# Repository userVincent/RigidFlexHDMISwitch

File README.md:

# Rigid Flex HDMI Switch PCB - Eagle Design

## Introduction
This document provides an overview of a Rigid Flex HDMI Switch PCB designed using Eagle..

## Design rules
- According to the design guide from Wurth Electronics, extra mechanical layers are utilized to 
denote the flexible and rigid sections of the PCB. The flexible portion of the PCB is outlined 
on Layer 113 (flex), while Layer 114 (rigid) is used to delineate the rigid section.
- The differential pairs in the design are routed with a spacing of 150 micrometers (um) and a 
trace width of 260um. This configuration ensures that the differential pairs maintain their 
characteristic impedance, which is crucial for signal integrity. Additionally, careful attention 
has been paid to maximize the distance between different differential pairs. This strategy is 
employed to minimize crosstalk.
- In this PCB design, Flex1 is the ground layer, providing a return path for current. Flex2 is the 
VCC layer, distributing power to the components. The top layer primarily carries signal traces, 
while the bottom layer is used for both signal routing and distributing a +5V power supply.
-  According to the design guide from Wurth Electronics, two additional (unconnected) tracks 
are incorporated on the outer edges of the PCB. This design feature is intended to enhance 
the rigidity of the flex section and decrease the likelihood of tearing, thereby improving the 
durability and longevity of the PCB.
- To ensure efficient power distribution and adequate heat dissipation for power components 
on the top layer, the design includes multiple vias and planes (top layer). These features 
enhance connectivity and allow heat to spread out efficiently.
- The decoupling capacitors for the TDMS351 are strategically positioned on the bottom layer, 
directly beneath the IC. This placement is chosen to ensure effective decoupling, providing a 
short path for current transients and reducing noise. This arrangement is also due to space 
constraints on the top layer, making the bottom layer a practical choice for accommodating 
these components.

## Layer Configuration
- **Top Layer:** Primarily for signal traces.
- **Flex1:** Ground layer for current return path.
- **Flex2:** VCC layer for power distribution.
- **Bottom Layer:** Used for signal routing and a +5V power supply.

## PCB Preview
- **Routing View**
  
- **Top View**  
  
- **Bottom View**  

## Conclusion
This README provides a basic guide to a Rigid Flex HDMI Switch PCB. For detailed design files and further information, refer to the included Eagle project files.

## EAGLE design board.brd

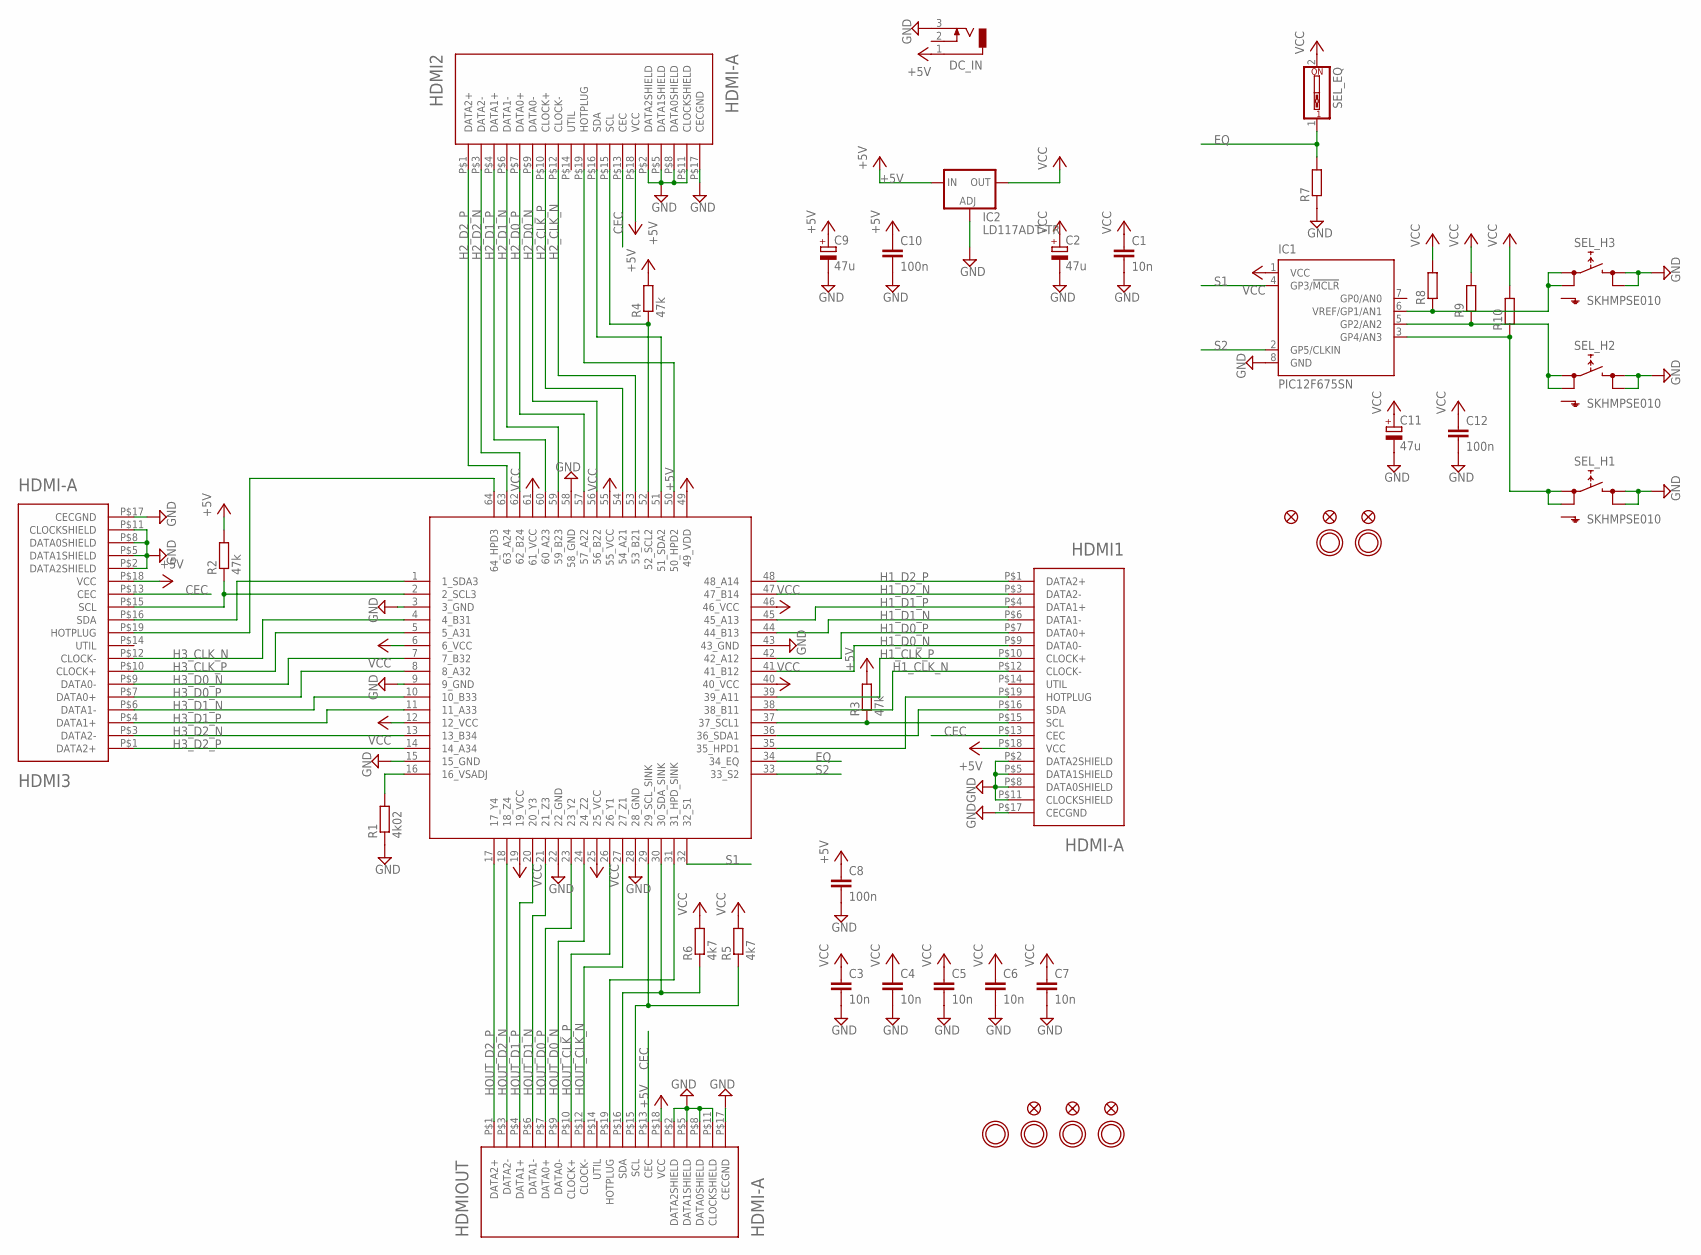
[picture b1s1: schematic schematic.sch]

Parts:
C1: 10n; C0402
C2, C9, C11: 47u; SMC_A
C3, C4, C5, C6, C7: 10n; 0402
C8: 100n; 0402
C10, C12: 100n; C0402
DC_IN: DCJ0303
FID1, FID2, FID3, FID4, FID5, FID6: FIDUCIAL""; FIDUCIAL_1MM
HDMI1, HDMI2, HDMI3: HDMI-A; HDMI_A
HDMIOUT: HDMI-A; HDMI_A
IC1: PIC12F675SN; SO-08
IC2: LD117ADT-TR; DPACK
R1: 4k02; 0402
R2, R3, R4: 47k; 0402
R5, R6: 4k7; 0402
R7, R8, R9, R10: R-EU_R0805; R0805
SEL_EQ: SW_DIP-1; EDG-01
SEL_H1, SEL_H2, SEL_H3: SKHMPSE010; SKHMPXE010
U1: TMDS351TQFP64; QFP50P1200X1200X120-64
U$1, U$2, U$31, U$32, U$33, U$34: MOUNTINGHOLE3.0; MOUNTINGHOLE_3.0_PLATED

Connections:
+5V: C8.1, C9.+, C10.1, DC_IN.1, HDMI1.P$18 (VCC), HDMI2.P$18 (VCC), HDMI3.P$18 (VCC), HDMIOUT.P$18 (VCC), IC2.3 (IN), R2.2, R3.2, R4.2, U1.49 (49_VDD)
CEC: HDMI1.P$13 (CEC), HDMI2.P$13 (CEC), HDMI3.P$13 (CEC), HDMIOUT.P$13 (CEC)
EQ: R7.2, SEL_EQ.1, U1.34 (34_EQ)
GND: C1.2, C2.-, C3.2, C4.2, C5.2, C6.2, C7.2, C8.2, C9.-, C10.2, C11.-, C12.2, DC_IN.3, HDMI1.P$2 (DATA2SHIELD), HDMI1.P$5 (DATA1SHIELD), HDMI1.P$8 (DATA0SHIELD), HDMI1.P$11 (CLOCKSHIELD), HDMI1.P$17 (CECGND), HDMI2.P$2 (DATA2SHIELD), HDMI2.P$5 (DATA1SHIELD), HDMI2.P$8 (DATA0SHIELD), HDMI2.P$11 (CLOCKSHIELD), HDMI2.P$17 (CECGND), HDMI3.P$2 (DATA2SHIELD), HDMI3.P$5 (DATA1SHIELD), HDMI3.P$8 (DATA0SHIELD), HDMI3.P$11 (CLOCKSHIELD), HDMI3.P$17 (CECGND), HDMIOUT.P$2 (DATA2SHIELD), HDMIOUT.P$5 (DATA1SHIELD), HDMIOUT.P$8 (DATA0SHIELD), HDMIOUT.P$11 (CLOCKSHIELD), HDMIOUT.P$17 (CECGND), IC1.8 (GND), IC2.1 (ADJ), R1.1, R7.1, SEL_H1.3 (2.1), SEL_H1.4 (2.2), SEL_H2.3 (2.1), SEL_H2.4 (2.2), SEL_H3.3 (2.1), SEL_H3.4 (2.2), U1.3 (3_GND), U1.9 (9_GND), U1.15 (15_GND), U1.22 (22_GND), U1.28 (28_GND), U1.43 (43_GND), U1.58 (58_GND)
H1_CLK_N: HDMI1.P$12 (CLOCK-), U1.38 (38_B11)
H1_CLK_P: HDMI1.P$10 (CLOCK+), U1.39 (39_A11)
H1_D0_N: HDMI1.P$9 (DATA0-), U1.41 (41_B12)
H1_D0_P: HDMI1.P$7 (DATA0+), U1.42 (42_A12)
H1_D1_N: HDMI1.P$6 (DATA1-), U1.44 (44_B13)
H1_D1_P: HDMI1.P$4 (DATA1+), U1.45 (45_A13)
H1_D2_N: HDMI1.P$3 (DATA2-), U1.47 (47_B14)
H1_D2_P: HDMI1.P$1 (DATA2+), U1.48 (48_A14)
H2_CLK_N: HDMI2.P$12 (CLOCK-), U1.53 (53_B21)
H2_CLK_P: HDMI2.P$10 (CLOCK+), U1.54 (54_A21)
H2_D0_N: HDMI2.P$9 (DATA0-), U1.56 (56_B22)
H2_D0_P: HDMI2.P$7 (DATA0+), U1.57 (57_A22)
H2_D1_N: HDMI2.P$6 (DATA1-), U1.59 (59_B23)
H2_D1_P: HDMI2.P$4 (DATA1+), U1.60 (60_A23)
H2_D2_N: HDMI2.P$3 (DATA2-), U1.62 (62_B24)
H2_D2_P: HDMI2.P$1 (DATA2+), U1.63 (63_A24)
H3_CLK_N: HDMI3.P$12 (CLOCK-), U1.4 (4_B31)
H3_CLK_P: HDMI3.P$10 (CLOCK+), U1.5 (5_A31)
H3_D0_N: HDMI3.P$9 (DATA0-), U1.7 (7_B32)
H3_D0_P: HDMI3.P$7 (DATA0+), U1.8 (8_A32)
H3_D1_N: HDMI3.P$6 (DATA1-), U1.10 (10_B33)
H3_D1_P: HDMI3.P$4 (DATA1+), U1.11 (11_A33)
H3_D2_N: HDMI3.P$3 (DATA2-), U1.13 (13_B34)
H3_D2_P: HDMI3.P$1 (DATA2+), U1.14 (14_A34)
HOUT_CLK_N: HDMIOUT.P$12 (CLOCK-), U1.27 (27_Z1)
HOUT_CLK_P: HDMIOUT.P$10 (CLOCK+), U1.26 (26_Y1)
HOUT_D0_N: HDMIOUT.P$9 (DATA0-), U1.24 (24_Z2)
HOUT_D0_P: HDMIOUT.P$7 (DATA0+), U1.23 (23_Y2)
HOUT_D1_N: HDMIOUT.P$6 (DATA1-), U1.21 (21_Z3)
HOUT_D1_P: HDMIOUT.P$4 (DATA1+), U1.20 (20_Y3)
HOUT_D2_N: HDMIOUT.P$3 (DATA2-), U1.18 (18_Z4)
HOUT_D2_P: HDMIOUT.P$1 (DATA2+), U1.17 (17_Y4)
unnamed: HDMI3.P$19 (HOTPLUG), U1.64 (64_HPD3)
unnamed: HDMI2.P$19 (HOTPLUG), U1.50 (50_HPD2)
unnamed: HDMI1.P$19 (HOTPLUG), U1.35 (35_HPD1)
unnamed: HDMIOUT.P$19 (HOTPLUG), U1.31 (31_HPD_SINK)
unnamed: HDMI3.P$16 (SDA), U1.1 (1_SDA3)
unnamed: HDMI3.P$15 (SCL), R2.1, U1.2 (2_SCL3)
unnamed: HDMI2.P$16 (SDA), U1.51 (51_SDA2)
unnamed: HDMI2.P$15 (SCL), R4.1, U1.52 (52_SCL2)
unnamed: HDMI1.P$15 (SCL), R3.1, U1.37 (37_SCL1)
unnamed: HDMI1.P$16 (SDA), U1.36 (36_SDA1)
unnamed: HDMIOUT.P$16 (SDA), R6.1, U1.30 (30_SDA_SINK)
unnamed: HDMIOUT.P$15 (SCL), R5.1, U1.29 (29_SCL_SINK)
unnamed: R1.2, U1.16 (16_VSADJ)
unnamed: IC1.6 (VREF/GP1/AN1), R8.1, SEL_H3.1 (1.1), SEL_H3.2 (1.2)
unnamed: IC1.5 (GP2/AN2), R9.1, SEL_H2.1 (1.1), SEL_H2.2 (1.2)
unnamed: IC1.3 (GP4/AN3), R10.1, SEL_H1.1 (1.1), SEL_H1.2 (1.2)
S1: IC1.4 (GP3/!MCLR), U1.32 (32_S1)
S2: IC1.2 (GP5/CLKIN), U1.33 (33_S2)
VCC: C1.1, C2.+, C3.1, C4.1, C5.1, C6.1, C7.1, C11.+, C12.1, IC1.1 (VCC), IC2.4 (OUT), R5.2, R6.2, R8.2, R9.2, R10.2, SEL_EQ.2, U1.6 (6_VCC), U1.12 (12_VCC), U1.19 (19_VCC), U1.25 (25_VCC), U1.40 (40_VCC), U1.46 (46_VCC), U1.55 (55_VCC), U1.61 (61_VCC)

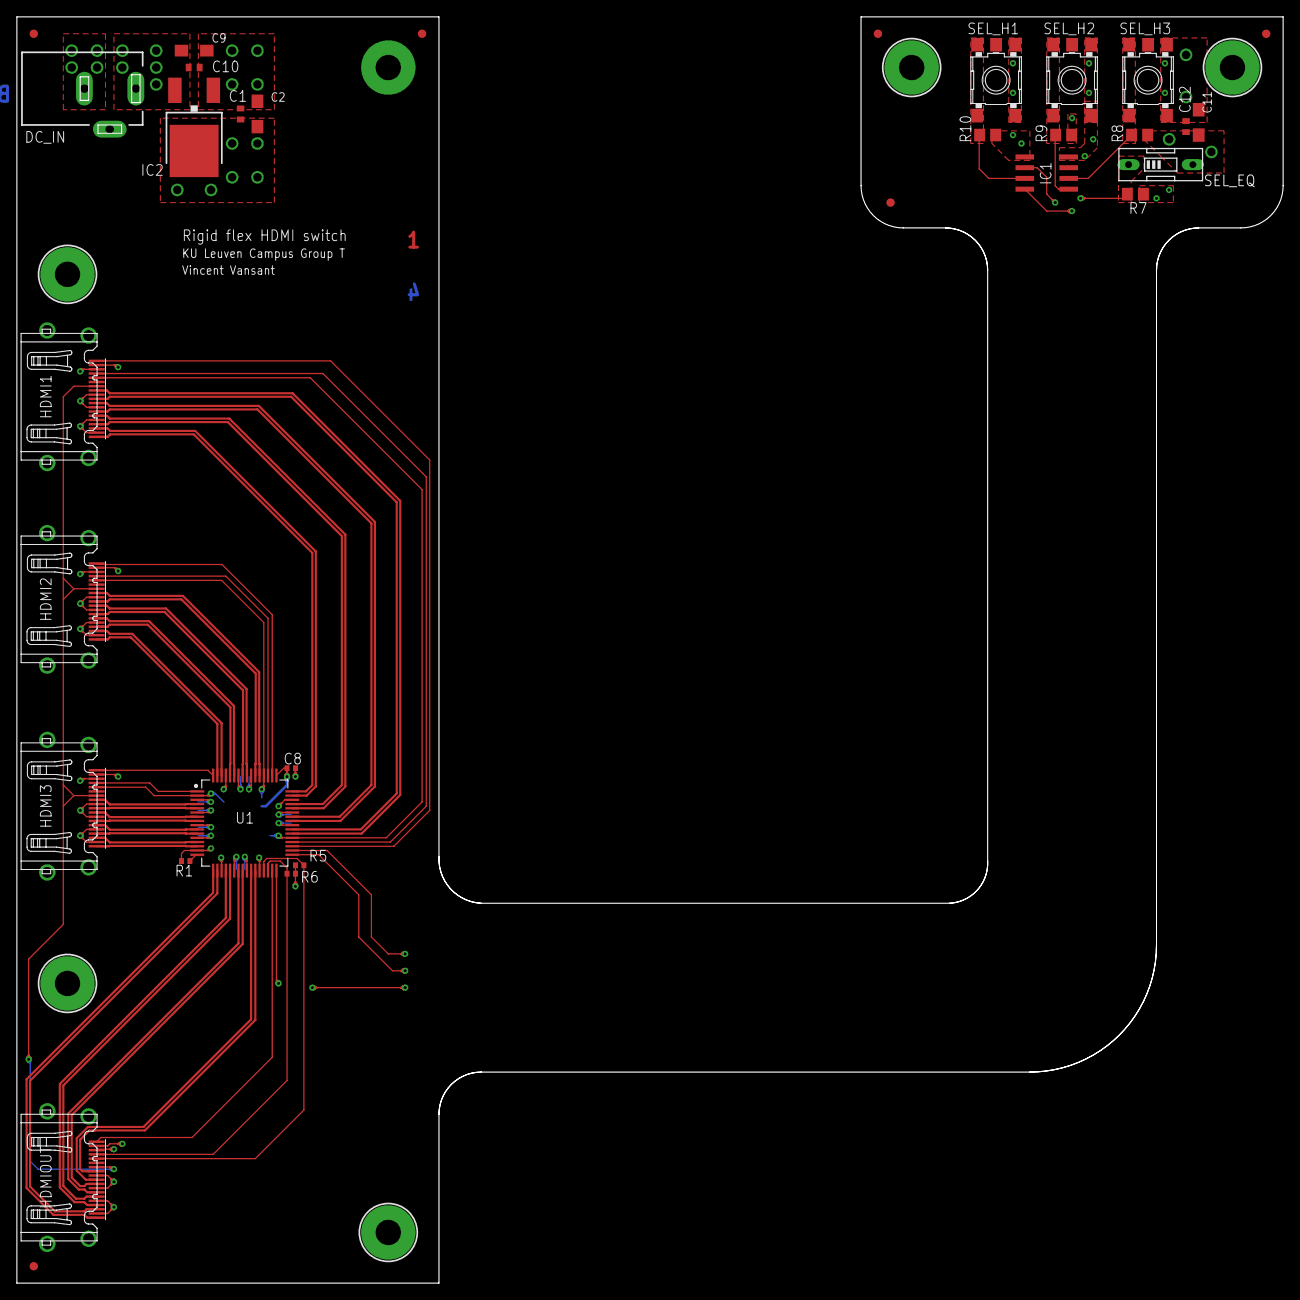
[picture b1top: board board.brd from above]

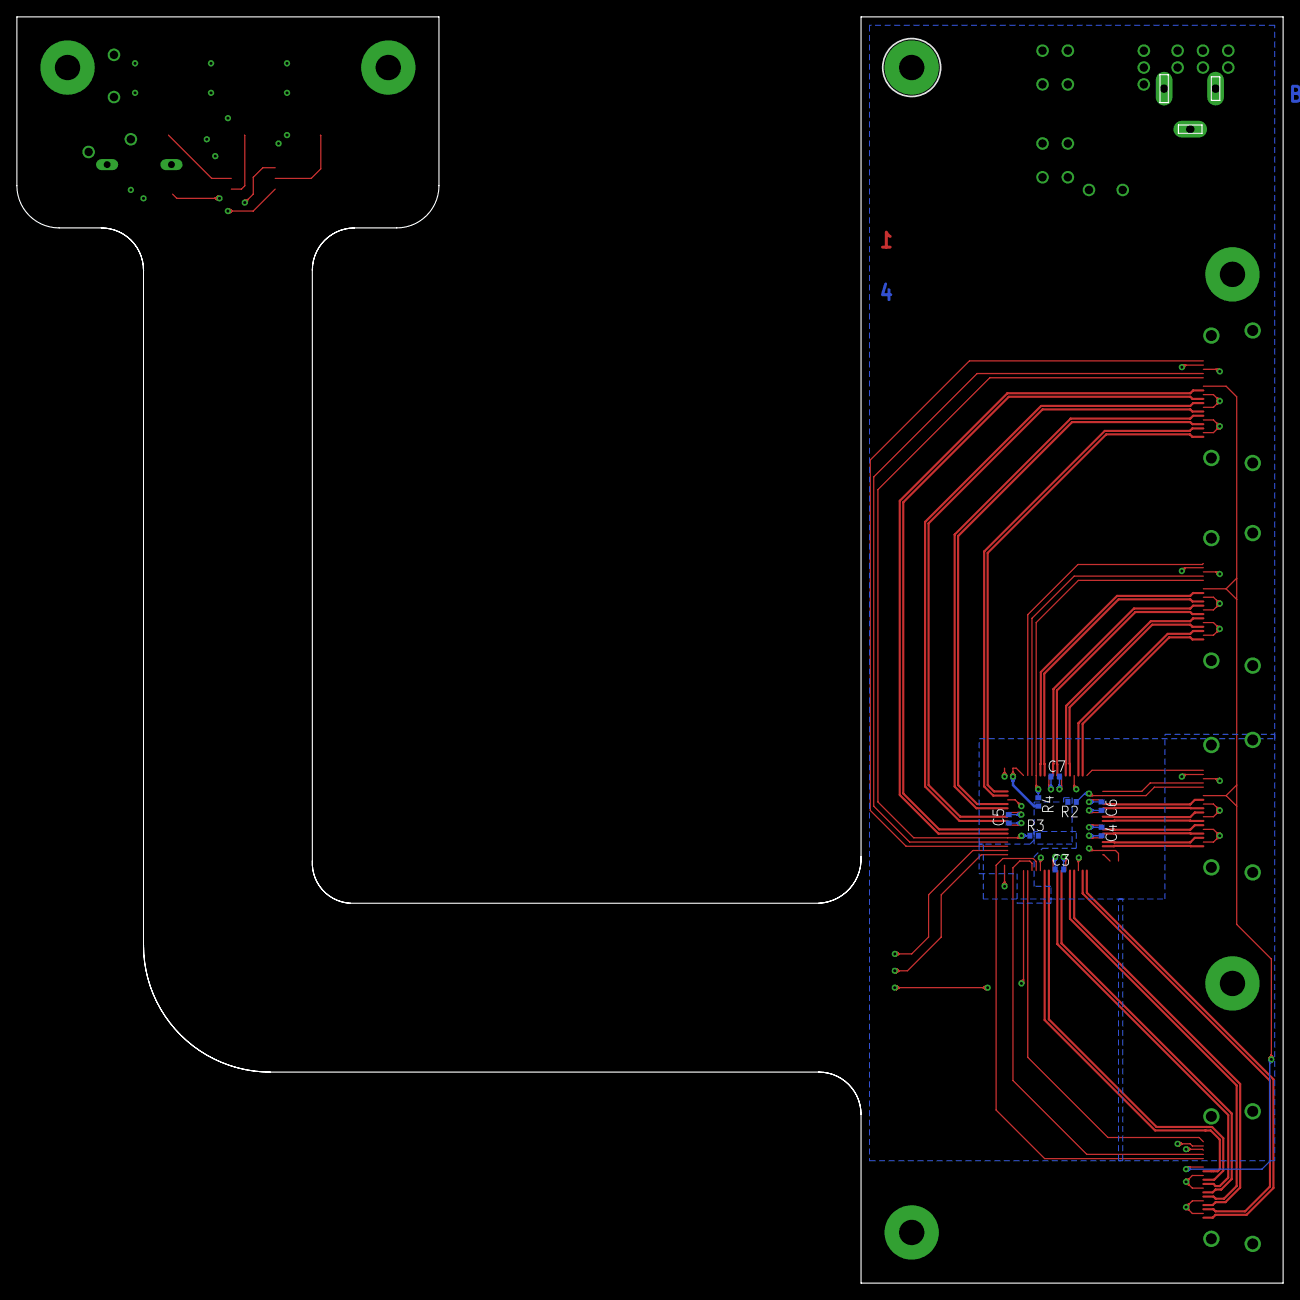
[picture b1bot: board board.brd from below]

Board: 4 copper layers, 150.0 x 150.0 mm, 46 parts (9 on the bottom side), 55 nets.

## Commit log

2024-01-28 added readme

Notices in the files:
parts and their libraries:
microbuilder: This work is placed in the public domain, and may be freely used for commercial and non-commercial work with the following conditions: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
